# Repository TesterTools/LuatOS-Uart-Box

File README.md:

# LuatOS-Uart-Box

基于LuatOS-SOC固件的低成本串口记录/输出设备，支持屏幕和TF卡。

## Kicad 需要添加的库

https://gitee.com/openLuat/kicad-symbols-libraries

https://github.com/chenxuuu/chenxuuu-kicad-lib

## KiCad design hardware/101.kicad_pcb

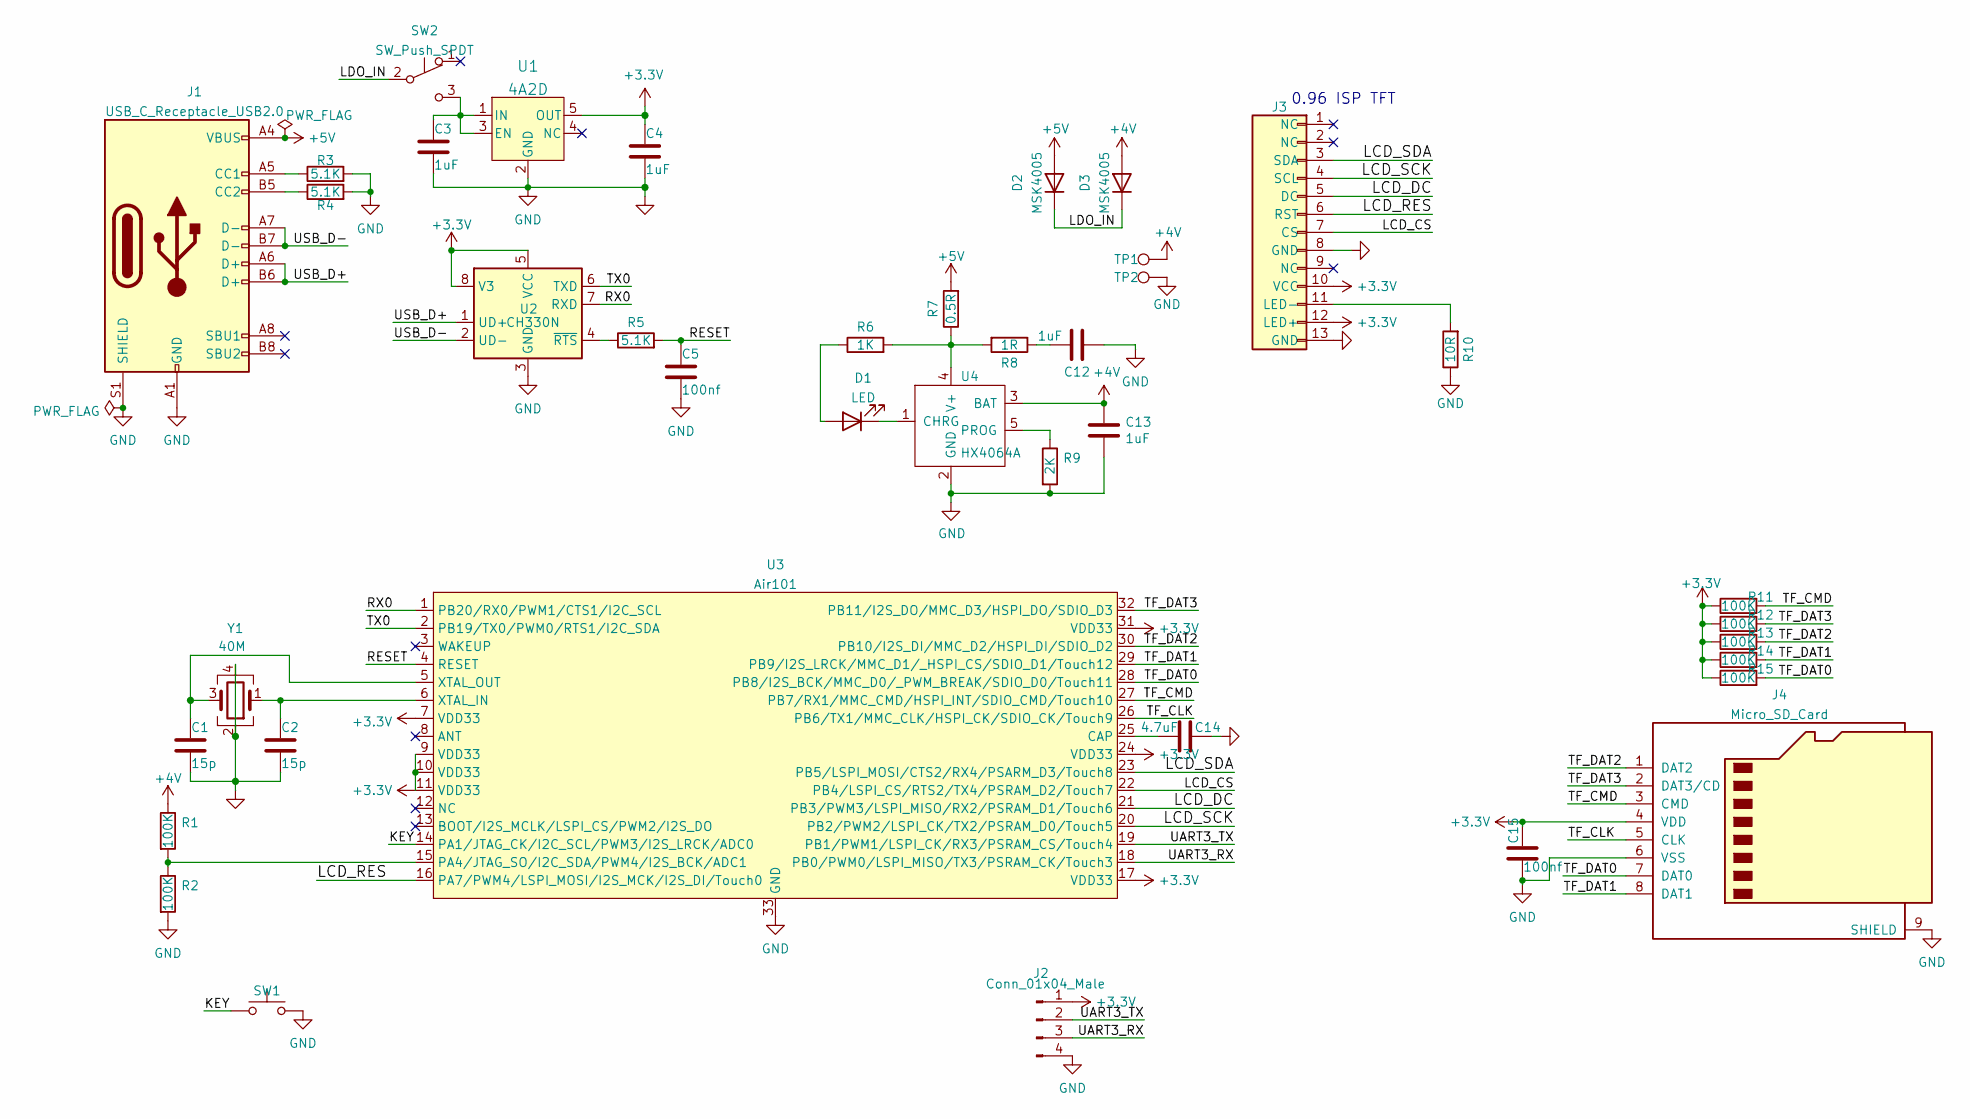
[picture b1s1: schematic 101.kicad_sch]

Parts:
C1, C2: 15p; C_0402_1005Metric
C3, C4, C12, C13: 1uF; C_0402_1005Metric
C5, C15: 100nf; C_0402_1005Metric
C14: 4.7uF; C_0402_1005Metric
D1: LED; LED_0402_1005Metric
D2, D3: MSK4005; D_SOD-523
J1: USB_C_Receptacle_USB2.0; USB_C_Receptacle_Palconn_UTC16-G
J2: Conn_01x04_Male; PinHeader_1x04_P2.54mm_Horizontal
J3: ST7735S-0.96TFT-13P
J4: Micro_SD_Card; microSD_TF
R1, R2, R11, R12, R13, R14, R15: 100K; R_0402_1005Metric
R3, R4, R5: 5.1K; R_0402_1005Metric
R6: 1K; R_0402_1005Metric
R7: 0.5R; R_0402_1005Metric
R8: 1R; R_0402_1005Metric
R9: 2K; R_0402_1005Metric
R10: 10R; R_0402_1005Metric
SW1: Side_SWITCH_SW_3*6*3.5mm; SW_SPST_B3U-3000P-B
SW2: SW_Push_SPDT; MSK-0002
TP1, TP2: TestPoint; TestPoint_Pad_2.0x2.0mm
U1: 4A2D; SOT-23-5
U2: CH330N; SOIC-8_3.9x4.9mm_P1.27mm
U3: Air101
U4: HX4064A; SOT-23-5
Y1: 40M; Crystal_SMD_3225-4Pin_3.2x2.5mm

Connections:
+3V3: C4.1, C15.1, J2.1, J3.10 (VCC), J3.12 (LED+), J4.4 (VDD), R11.1, R12.1, R13.1, R14.1, R15.1, U1.5 (OUT), U2.5 (VCC), U2.8 (V3), U3.7 (VDD33), U3.9 (VDD33), U3.10 (VDD33), U3.11 (VDD33), U3.17 (VDD33), U3.24 (VDD33), U3.31 (VDD33)
+4V: C13.1, D3.2 (A), R1.1, TP1.1, U4.3 (BAT)
+5V: D2.2 (A), J1.A4 (VBUS), J1.A9 (VBUS), J1.B4 (VBUS), J1.B9 (VBUS), R7.2
/KEY: SW1.1, U3.14 (PA1/JTAG_CK/I2C_SCL/PWM3/I2S_LRCK/ADC0)
/LCD_CS: J3.7 (CS), U3.22 (PB4/LSPI_CS/RTS2/TX4/PSRAM_D2/Touch7)
/LCD_DC: J3.5 (DC), U3.21 (PB3/PWM3/LSPI_MISO/RX2/PSRAM_D1/Touch6)
/LCD_RES: J3.6 (RST), U3.16 (PA7/PWM4/LSPI_MOSI/I2S_MCK/I2S_DI/Touch0)
/LCD_SCK: J3.4 (SCL), U3.20 (PB2/PWM2/LSPI_CK/TX2/PSRAM_D0/Touch5)
/LCD_SDA: J3.3 (SDA), U3.23 (PB5/LSPI_MOSI/CTS2/RX4/PSARM_D3/Touch8)
/LDO_IN: D2.1 (K), D3.1 (K), SW2.2 (B)
/RESET: C5.1, R5.2, U3.4 (RESET)
/RX0: U2.7 (RXD), U3.1 (PB20/RX0/PWM1/CTS1/I2C_SCL)
/TF_CLK: J4.5 (CLK), U3.26 (PB6/TX1/MMC_CLK/HSPI_CK/SDIO_CK/Touch9)
/TF_CMD: J4.3 (CMD), R11.2, U3.27 (PB7/RX1/MMC_CMD/HSPI_INT/SDIO_CMD/Touch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)
/TF_DAT0: J4.7 (DAT0), R15.2, U3.28 (PB8/I2S_BCK/MMC_D0/_PWM_BREAK/SDIO_D0/T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)
/TF_DAT1: J4.8 (DAT1), R14.2, U3.29 (PB9/I2S_LRCK/MMC_D1/_HSPI_CS/SDIO_D1/To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)
/TF_DAT2: J4.1 (DAT2), R13.2, U3.30 (PB10/I2S_DI/MMC_D2/HSPI_DI/SDIO_D2)
/TF_DAT3: J4.2 (DAT3/CD), R12.2, U3.32 (PB11/I2S_DO/MMC_D3/HSPI_DO/SDIO_D3)
/TX0: U2.6 (TXD), U3.2 (PB19/TX0/PWM0/RTS1/I2C_SDA)
/UART3_RX: J2.3, U3.18 (PB0/PWM0/LSPI_MISO/TX3/PSRAM_CK/Touch3)
/UART3_TX: J2.2, U3.19 (PB1/PWM1/LSPI_CK/RX3/PSRAM_CS/Touch4)
/USB_D+: J1.A6 (D+), J1.B6 (D+), U2.1 (UD+)
/USB_D-: J1.A7 (D-), J1.B7 (D-), U2.2 (UD-)
GND: C1.2, C2.2, C3.2, C4.2, C5.2, C12.2, C13.2, C14.1, C15.2, J1.A1 (GND), J1.A12 (GND), J1.B1 (GND), J1.B12 (GND), J1.S1 (SHIELD), J2.4, J3.8 (GND), J3.13 (GND), J4.6 (VSS), J4.9 (SHIELD), R2.2, R3.2, R4.2, R9.2, R10.1, SW1.2, TP2.1, U1.2 (GND), U2.3 (GND), U3.33 (GND), U4.2 (GND), Y1.2, Y1.4
unnamed: C1.1, U3.5 (XTAL_OUT), Y1.3
unnamed: C2.1, U3.6 (XTAL_IN), Y1.1
unnamed: C3.1, SW2.3 (C), U1.1 (IN), U1.3 (EN)
unnamed: C12.1, R8.1
unnamed: C14.2, U3.25 (CAP)
unnamed: D1.1 (K), U4.1 (CHRG)
unnamed: D1.2 (A), R6.1
unnamed: J1.A5 (CC1), R3.1
unnamed: J1.B5 (CC2), R4.1
unnamed: J3.11 (LED-), R10.2
unnamed: R1.2, R2.1, U3.15 (PA4/JTAG_SO/I2C_SDA/PWM4/I2S_BCK/ADC1)
unnamed: R5.1, U2.4 (~RTS)
unnamed: R6.2, R7.1, R8.2, U4.4 (V+)
unnamed: R9.1, U4.5 (PROG)

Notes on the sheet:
0.96 ISP TFT

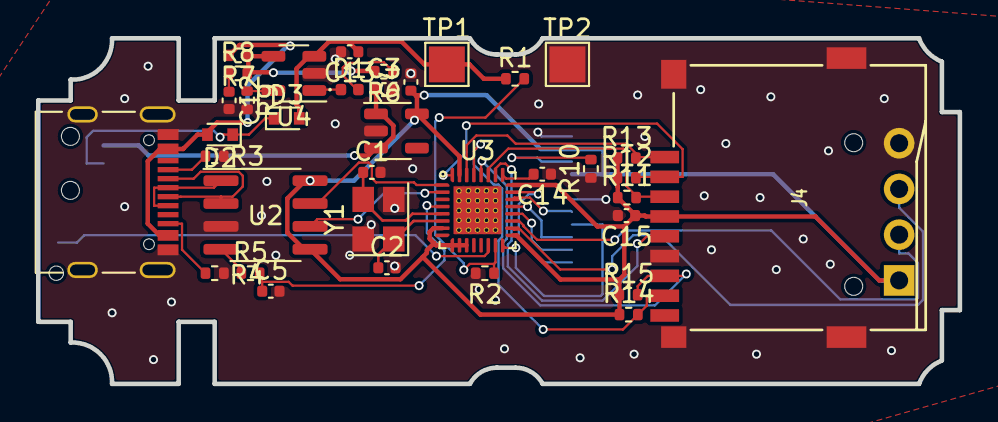
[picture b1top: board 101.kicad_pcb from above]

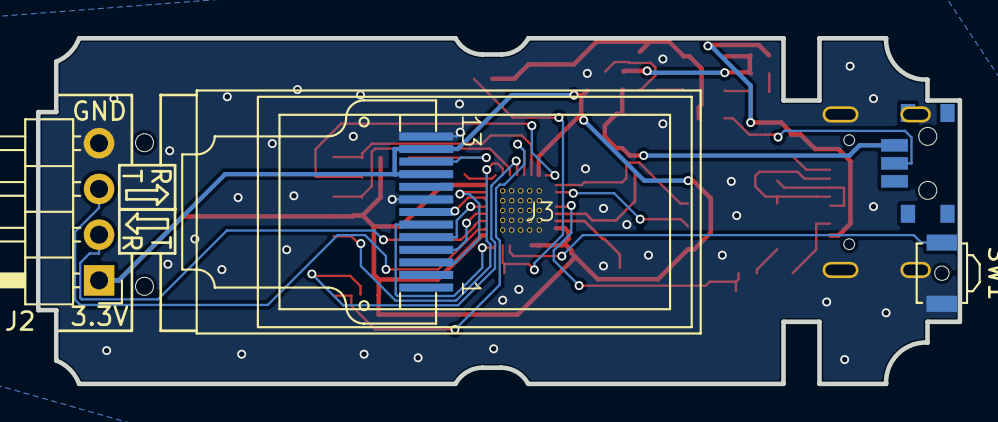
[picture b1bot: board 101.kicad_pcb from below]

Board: 2 copper layers, 51.2 x 19.2 mm, 40 parts (4 on the bottom side), 38 nets.

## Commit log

2021-11-10 update: 小改目录结构
2021-11-10 update: 初始化
2021-11-23 update: 原理图好了
2021-11-23 update: 分配封装
2021-11-24 add: 随便画了画pcb
2021-11-24 update: 小改，然后下单
